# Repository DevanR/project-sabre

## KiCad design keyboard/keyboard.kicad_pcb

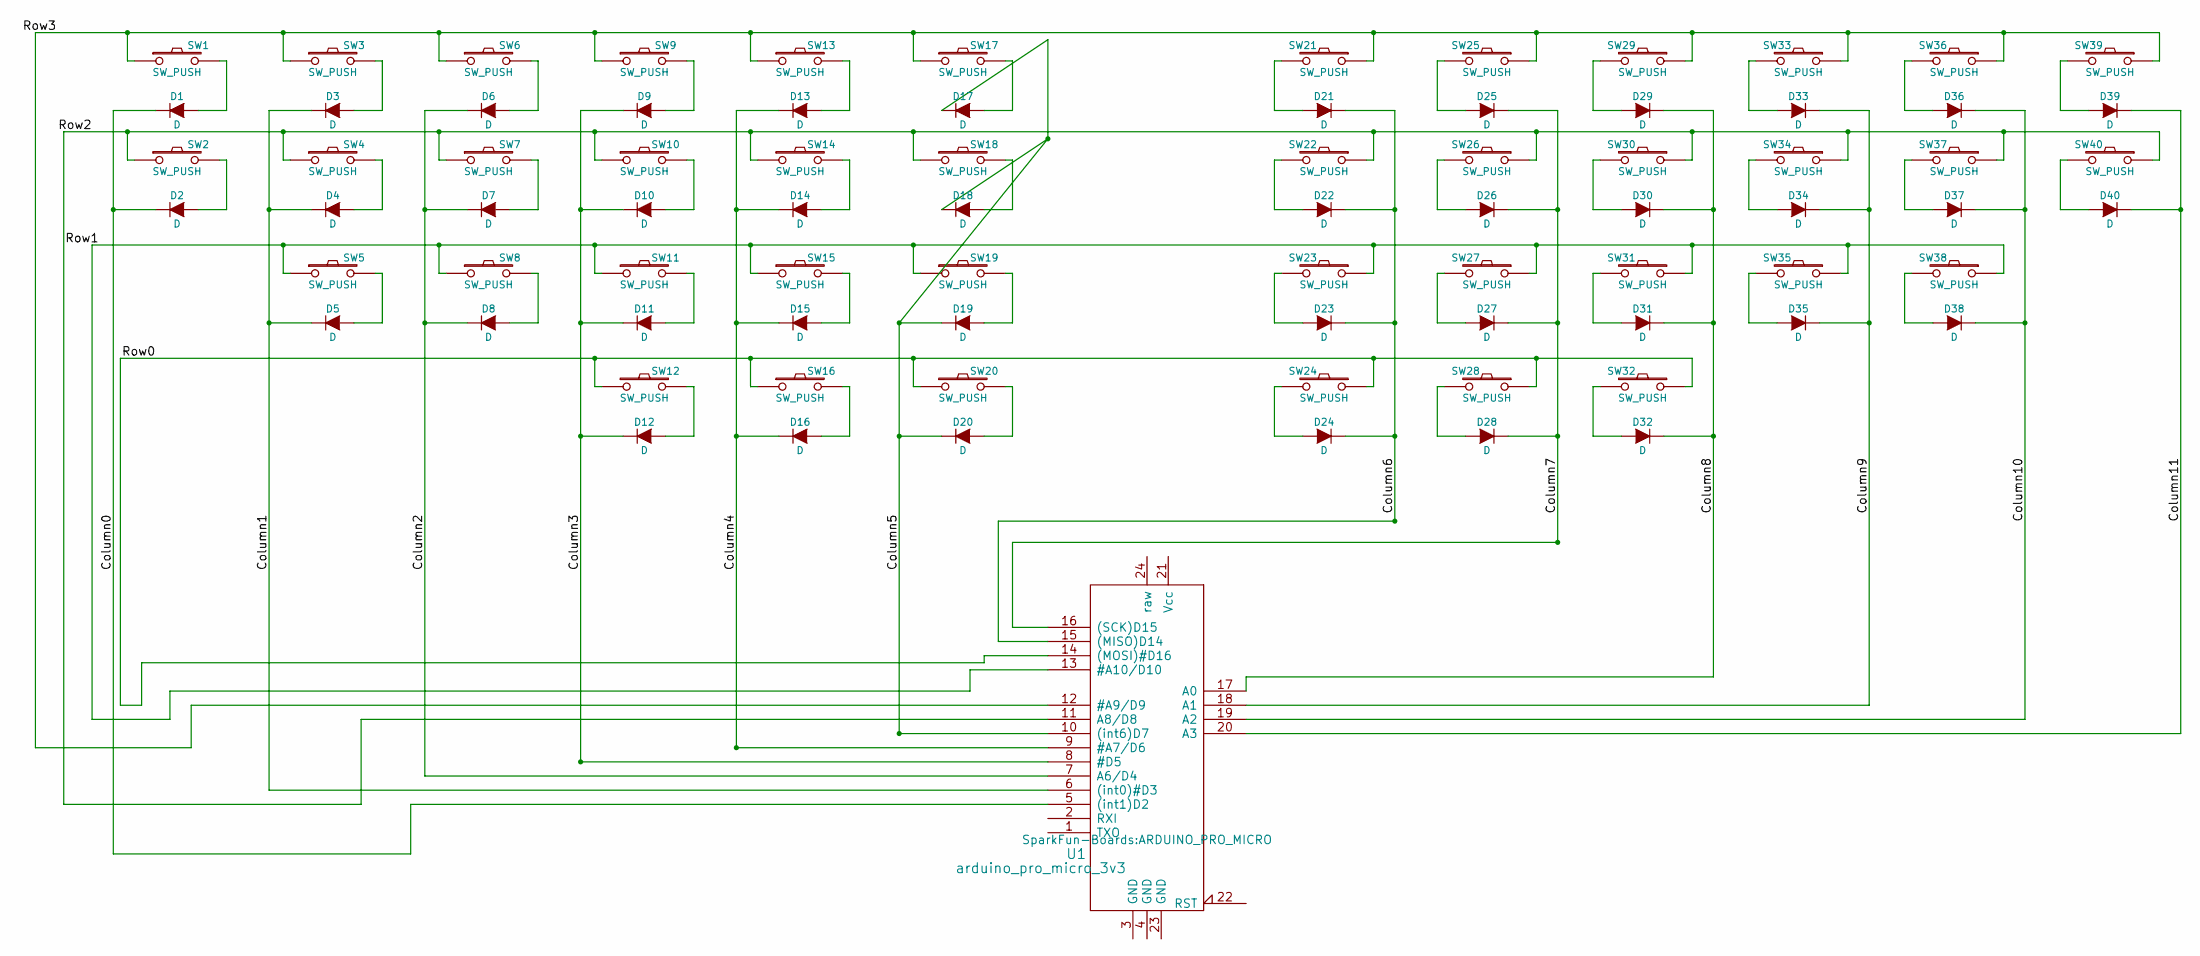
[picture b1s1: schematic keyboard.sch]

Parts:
D1, D2, D3, D4, D5, D6, D7, D8, D9, D10, D11, D12, D13, D14, D15, D16, D17, D18, D19, D20, D21, D22, D23, D24, D25, D26, D27, D28, D29, D30, D31, D32, D33, D34, D35, D36, D37, D38, D39, D40: D; DIODE
SW1, SW2, SW3, SW4, SW5, SW6, SW7, SW8, SW9, SW10, SW11, SW12, SW13, SW14, SW15, SW16, SW17, SW18, SW19, SW20, SW21, SW22, SW23, SW24, SW25, SW26, SW27, SW28, SW29, SW30, SW31, SW32, SW33, SW34, SW35, SW36, SW37, SW38, SW39, SW40: SW_PUSH; CHERRY_PCB_100H
U1: arduino_pro_micro_3v3; ARDUINO_PRO_MICRO

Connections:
/Column0: D1.1 (K), D2.1 (K), U1.5 ((int1)D2)
/Column1: D3.1 (K), D4.1 (K), D5.1 (K), U1.6 ((int0)#D3)
/Column2: D6.1 (K), D7.1 (K), D8.1 (K), U1.7 (A6/D4)
/Column3: D9.1 (K), D10.1 (K), D11.1 (K), D12.1 (K), U1.8 (#D5)
/Column4: D13.1 (K), D14.1 (K), D15.1 (K), D16.1 (K), U1.9 (#A7/D6)
/Column5: D17.1 (K), D18.1 (K), D19.1 (K), D20.1 (K), U1.10 ((int6)D7)
/Column6: D21.1 (K), D22.1 (K), D23.1 (K), D24.1 (K), U1.15 ((MISO)D14)
/Column7: D25.1 (K), D26.1 (K), D27.1 (K), D28.1 (K), U1.16 ((SCK)D15)
/Column8: D29.1 (K), D30.1 (K), D31.1 (K), D32.1 (K), U1.17 (A0)
/Column9: D33.1 (K), D34.1 (K), D35.1 (K), U1.18 (A1)
/Column10: D36.1 (K), D37.1 (K), D38.1 (K), U1.19 (A2)
/Column11: D39.1 (K), D40.1 (K), U1.20 (A3)
/Row0: SW12.1, SW16.1, SW20.1, SW24.1, SW28.1, SW32.1, U1.14 ((MOSI)#D16)
/Row1: SW5.1, SW8.1, SW11.1, SW15.1, SW19.1, SW23.1, SW27.1, SW31.1, SW35.1, SW38.1, U1.13 (#A10/D10)
/Row2: SW2.1, SW4.1, SW7.1, SW10.1, SW14.1, SW18.1, SW22.1, SW26.1, SW30.1, SW34.1, SW37.1, SW40.1, U1.11 (A8/D8)
/Row3: SW1.1, SW3.1, SW6.1, SW9.1, SW13.1, SW17.1, SW21.1, SW25.1, SW29.1, SW33.1, SW36.1, SW39.1, U1.12 (#A9/D9)
unnamed: D1.2 (A), SW1.2
unnamed: D2.2 (A), SW2.2
unnamed: D3.2 (A), SW3.2
unnamed: D4.2 (A), SW4.2
unnamed: D5.2 (A), SW5.2
unnamed: D6.2 (A), SW6.2
unnamed: D7.2 (A), SW7.2
unnamed: D8.2 (A), SW8.2
unnamed: D9.2 (A), SW9.2
unnamed: D10.2 (A), SW10.2
unnamed: D11.2 (A), SW11.2
unnamed: D12.2 (A), SW12.2
unnamed: D13.2 (A), SW13.2
unnamed: D14.2 (A), SW14.2
unnamed: D15.2 (A), SW15.2
unnamed: D16.2 (A), SW16.2
unnamed: D17.2 (A), SW17.2
unnamed: D18.2 (A), SW18.2
unnamed: D19.2 (A), SW19.2
unnamed: D20.2 (A), SW20.2
unnamed: D21.2 (A), SW21.2
unnamed: D22.2 (A), SW22.2
unnamed: D23.2 (A), SW23.2
unnamed: D24.2 (A), SW24.2
unnamed: D25.2 (A), SW25.2
unnamed: D26.2 (A), SW26.2
unnamed: D27.2 (A), SW27.2
unnamed: D28.2 (A), SW28.2
unnamed: D29.2 (A), SW29.2
unnamed: D30.2 (A), SW30.2
unnamed: D31.2 (A), SW31.2
unnamed: D32.2 (A), SW32.2
unnamed: D33.2 (A), SW33.2
unnamed: D34.2 (A), SW34.2
unnamed: D35.2 (A), SW35.2
unnamed: D36.2 (A), SW36.2
unnamed: D37.2 (A), SW37.2
unnamed: D38.2 (A), SW38.2
unnamed: D39.2 (A), SW39.2
unnamed: D40.2 (A), SW40.2

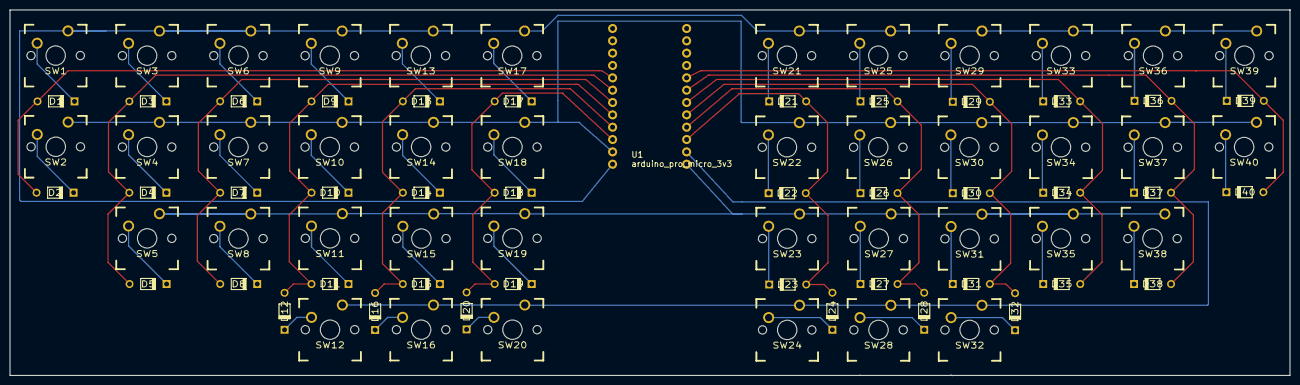
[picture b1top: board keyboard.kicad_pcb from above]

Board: 2 copper layers, 263.5 x 75.2 mm, 81 parts (0 on the bottom side), 56 nets.

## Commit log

2016-05-05 moved files from dropbox
